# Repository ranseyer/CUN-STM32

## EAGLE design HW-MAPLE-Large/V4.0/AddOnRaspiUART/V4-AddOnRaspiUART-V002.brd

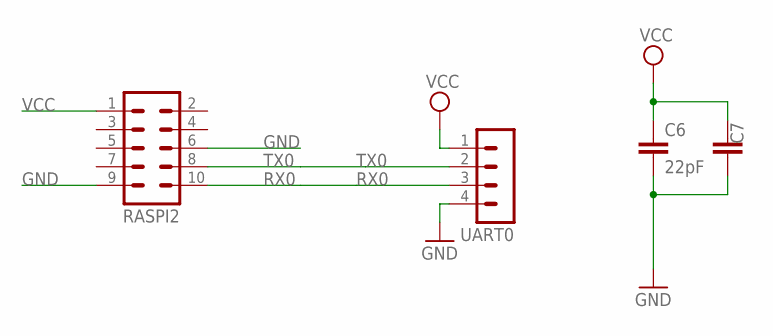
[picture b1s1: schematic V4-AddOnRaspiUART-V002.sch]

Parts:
C6: 22pF; C0805
C7: C-EUC1812; C1812
RASPI2: MA05-2
UART0: MA04-1

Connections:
GND: C6.2, C7.1, RASPI2.6, RASPI2.9, UART0.4
RX0: RASPI2.10, UART0.3
TX0: RASPI2.8, UART0.2
VCC: C6.1, C7.2, RASPI2.1, UART0.1

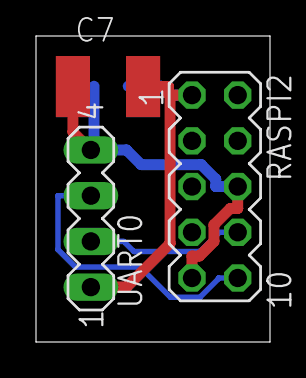
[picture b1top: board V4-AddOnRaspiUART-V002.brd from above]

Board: 2 copper layers, 13.0 x 17.0 mm, 4 parts (1 on the bottom side), 4 nets.

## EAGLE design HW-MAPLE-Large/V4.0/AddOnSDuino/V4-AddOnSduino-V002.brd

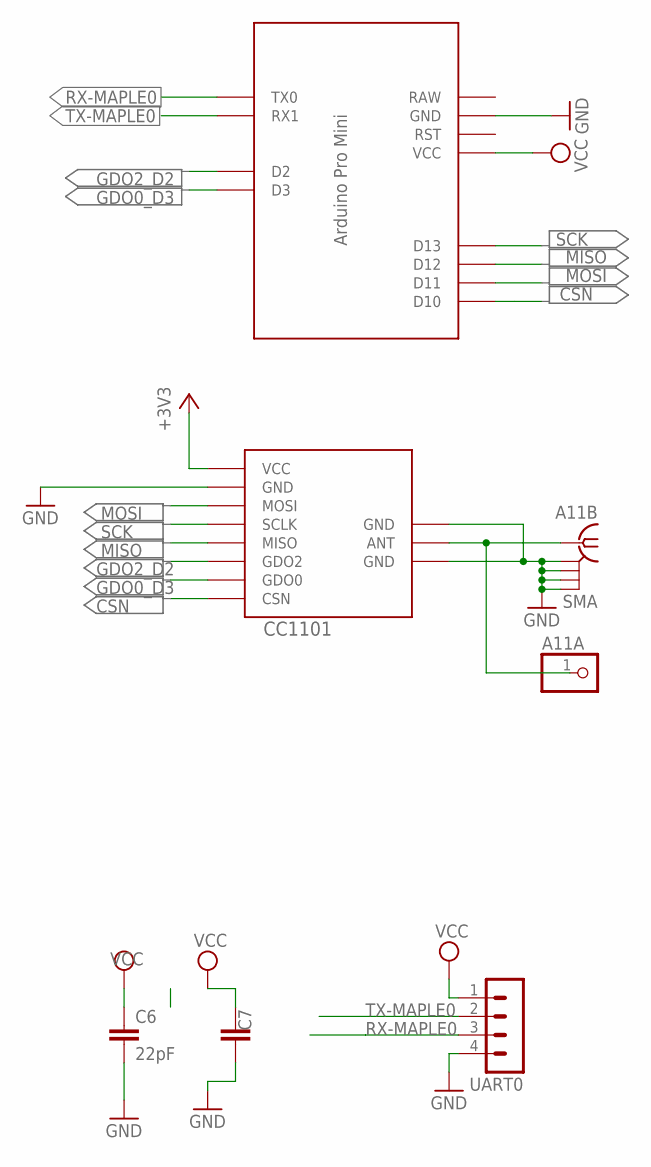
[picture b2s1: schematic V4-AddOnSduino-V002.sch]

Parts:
A11A: PINHD-1X1; 1X01
A11B: SMA
C6: 22pF; C0805
C7: C-EUC1812; C1812
CC1101: CC1101_MODULE1SMD; CC1101_MODULE1_SMD
U$2: MARTIN-PROMINI-CC1101; MARTIN-PRO-CC1101
UART0: MA04-1

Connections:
+3V3: CC1101.VCC
ANT1: A11A.1, A11B.1, CC1101.ANT
CSN: CC1101.CSN, U$2.D10
GDO0_D3: CC1101.GDO0, U$2.D3
GDO2_D2: CC1101.GDO2, U$2.D2
GND: A11B.GND@1 (2), A11B.GND@2 (3), A11B.GND@3 (4), A11B.GND@4 (5), C6.2, C7.1, CC1101.GND@0 (GND), CC1101.GND@1 (GND), CC1101.GND@2 (GND), U$2.GND, UART0.4
MISO: CC1101.MISO, U$2.D12
MOSI: CC1101.MOSI, U$2.D11
RX-MAPLE0: U$2.TX0, UART0.3
SCK: CC1101.SCLK, U$2.D13
TX-MAPLE0: U$2.RX1, UART0.2
VCC: C6.1, C7.2, U$2.VCC, UART0.1

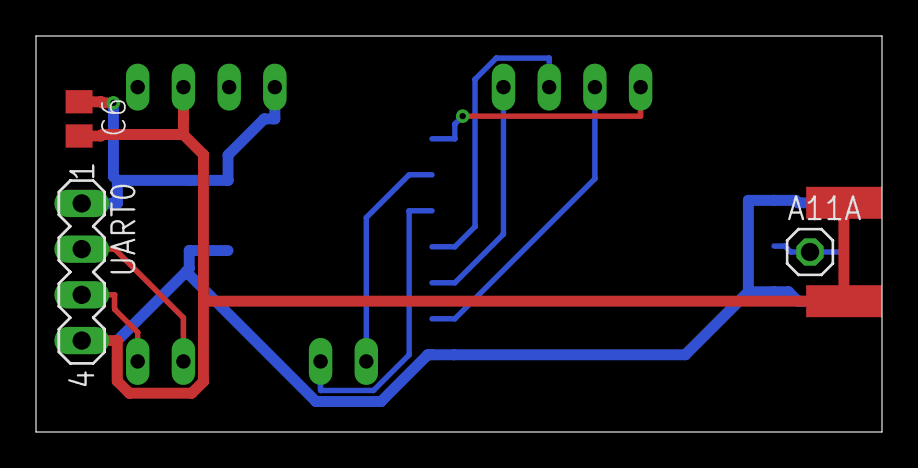
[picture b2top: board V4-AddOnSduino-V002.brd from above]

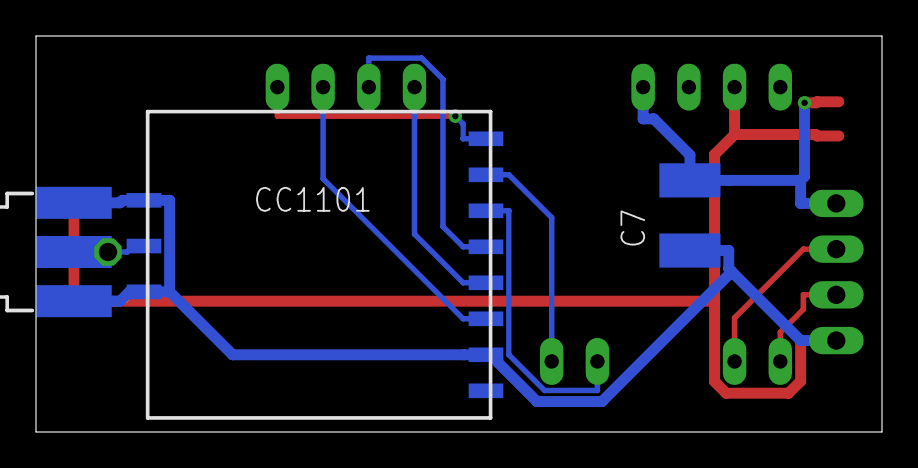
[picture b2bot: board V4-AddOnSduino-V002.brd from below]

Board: 2 copper layers, 47.0 x 22.0 mm, 7 parts (3 on the bottom side), 11 nets.

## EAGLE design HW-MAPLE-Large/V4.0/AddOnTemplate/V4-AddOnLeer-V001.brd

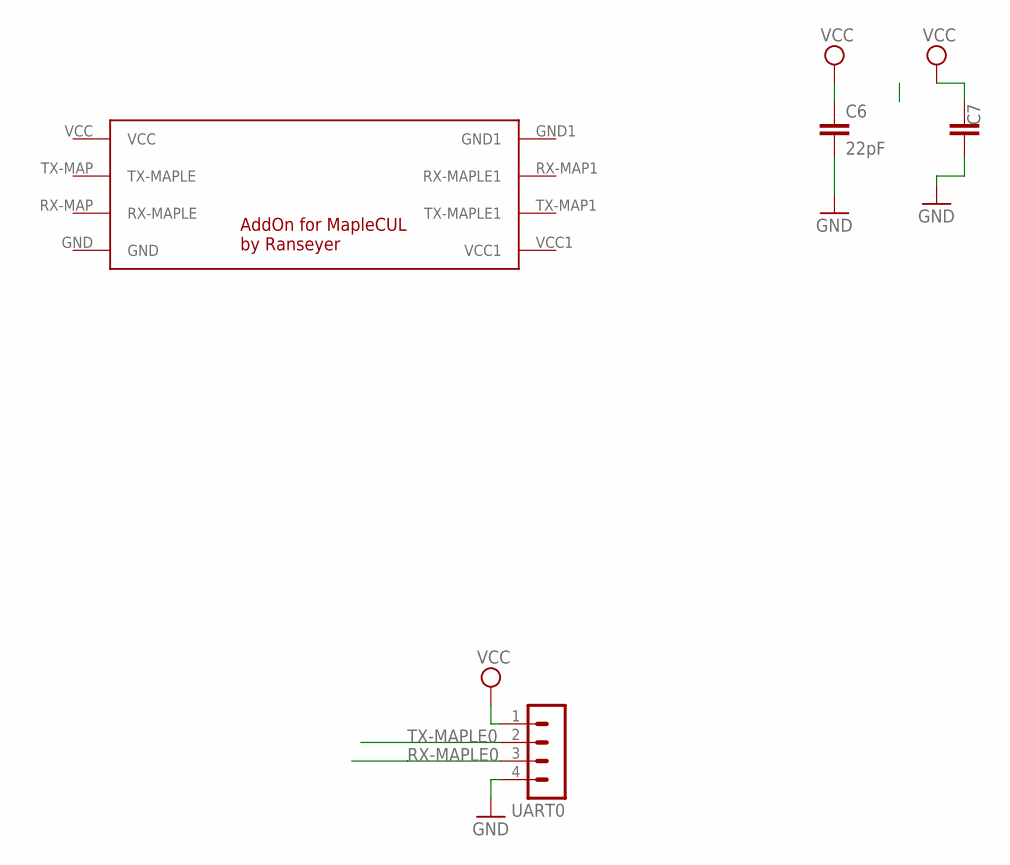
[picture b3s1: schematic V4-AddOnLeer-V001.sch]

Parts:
C6: 22pF; C0805
C7: C-EUC1812; C1812
U$1: MAPLE-CUL-ADDON-V01; MAPLE-CUL-V01
UART0: MA04-1

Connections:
GND: C6.2, C7.1, UART0.4
RX-MAPLE0: UART0.3
TX-MAPLE0: UART0.2
VCC: C6.1, C7.2, UART0.1

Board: 2 copper layers, 4 parts (1 on the bottom side), 2 nets, no tracks yet.

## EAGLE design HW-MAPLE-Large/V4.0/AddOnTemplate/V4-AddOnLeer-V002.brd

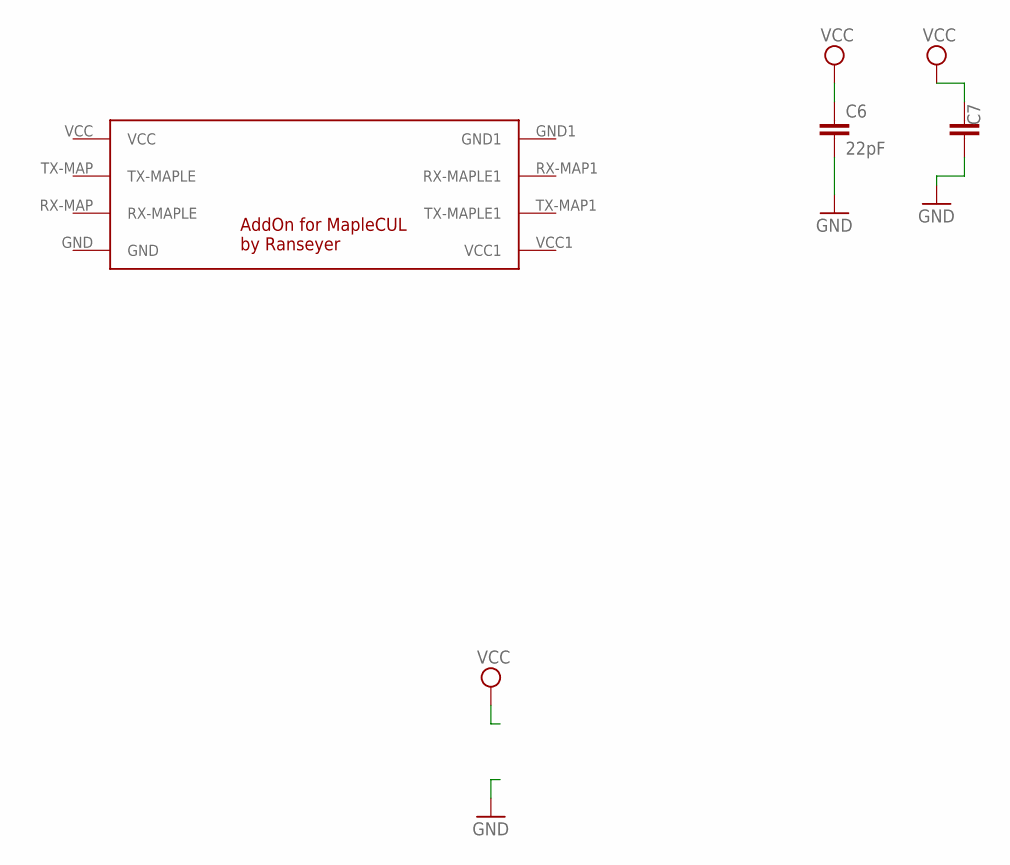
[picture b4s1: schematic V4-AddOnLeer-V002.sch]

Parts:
C6: 22pF; C0805
C7: C-EUC1812; C1812
U$1: MAPLE-CUL-ADDON-V01; MAPLE-CUL-V01

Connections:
GND: C6.2, C7.1
VCC: C6.1, C7.2

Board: 2 copper layers, 3 parts (1 on the bottom side), 2 nets, no tracks yet.

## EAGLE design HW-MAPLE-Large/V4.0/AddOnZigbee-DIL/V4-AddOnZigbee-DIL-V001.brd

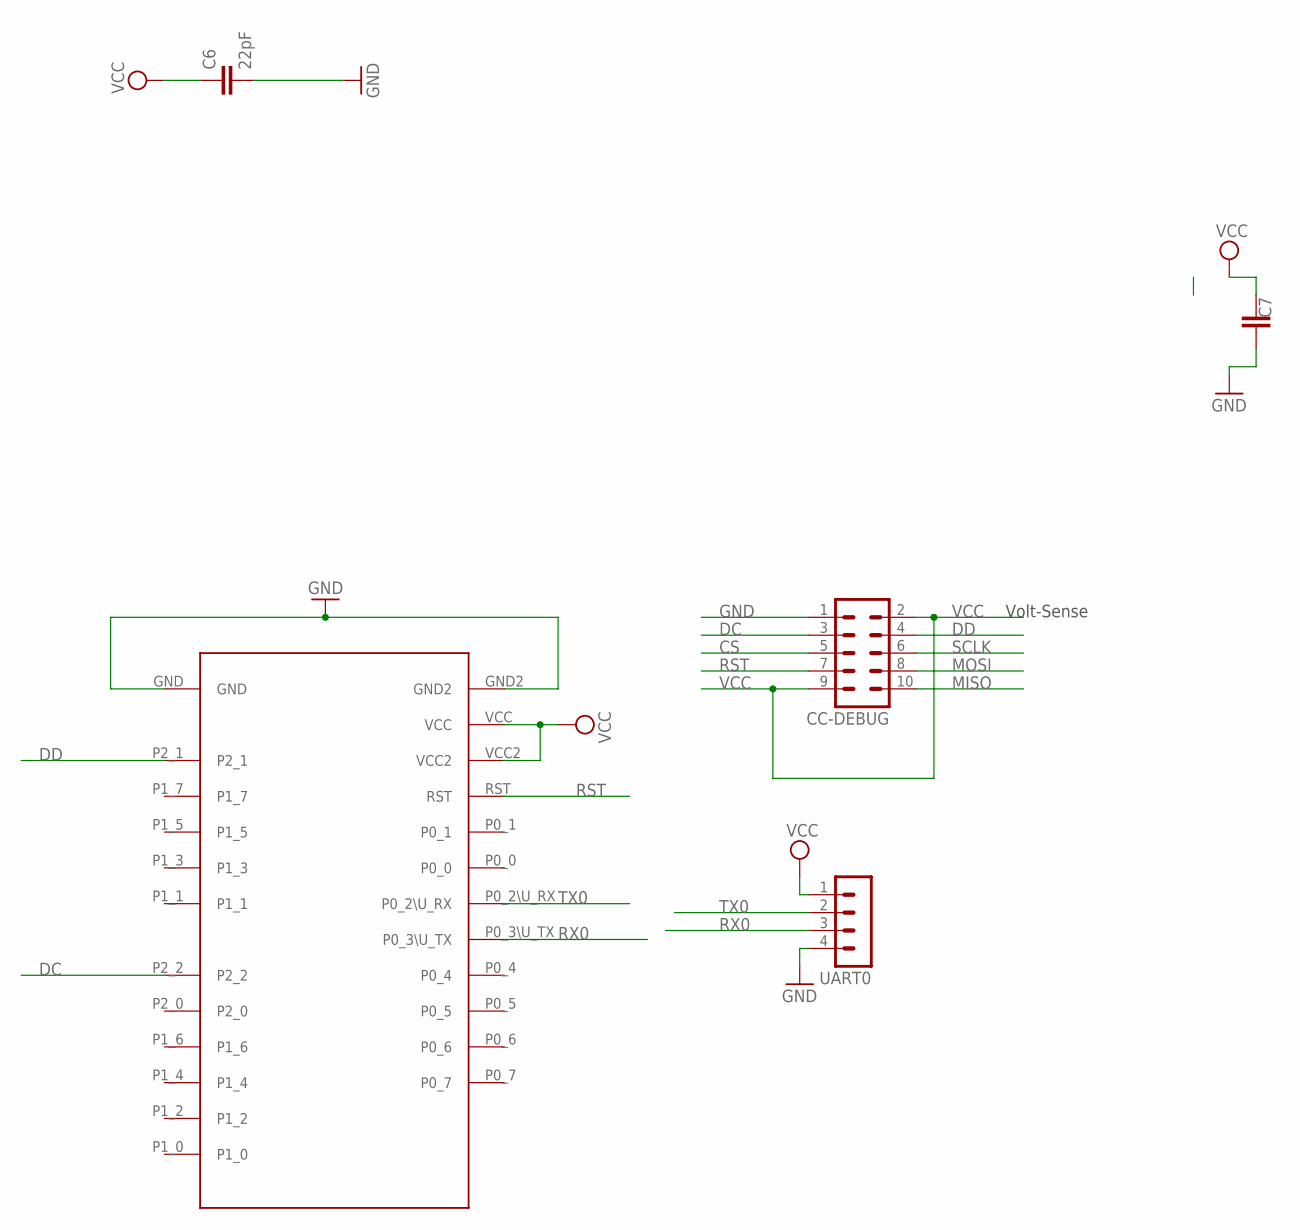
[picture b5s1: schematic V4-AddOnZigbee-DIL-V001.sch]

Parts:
C6: 22pF; C0805
C7: C-EUC1812; C1812
CC-DEBUG: MA05-2
U$3: CC2530_MODULE; CC2530_DIL
UART0: MA04-1

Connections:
CS: CC-DEBUG.5
DC: CC-DEBUG.3, U$3.P2_2
DD: CC-DEBUG.4, U$3.P2_1
GND: C6.2, C7.1, CC-DEBUG.1, U$3.GND, U$3.GND2, UART0.4
MISO: CC-DEBUG.10
MOSI: CC-DEBUG.8
RST: CC-DEBUG.7, U$3.RST
RX0: U$3.P0_3\U_TX, UART0.3
SCLK: CC-DEBUG.6
TX0: U$3.P0_2\U_RX, UART0.2
VCC: C6.1, C7.2, CC-DEBUG.2, CC-DEBUG.9, U$3.VCC, U$3.VCC2, UART0.1

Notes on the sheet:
Volt-Sense

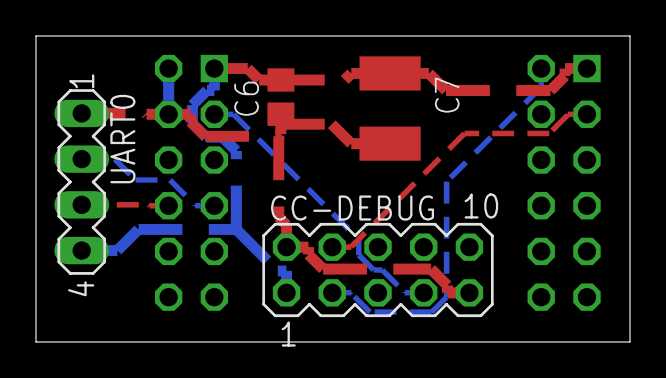
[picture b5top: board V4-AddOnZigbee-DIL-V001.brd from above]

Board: 2 copper layers, 33.0 x 17.0 mm, 5 parts (1 on the bottom side), 7 nets.

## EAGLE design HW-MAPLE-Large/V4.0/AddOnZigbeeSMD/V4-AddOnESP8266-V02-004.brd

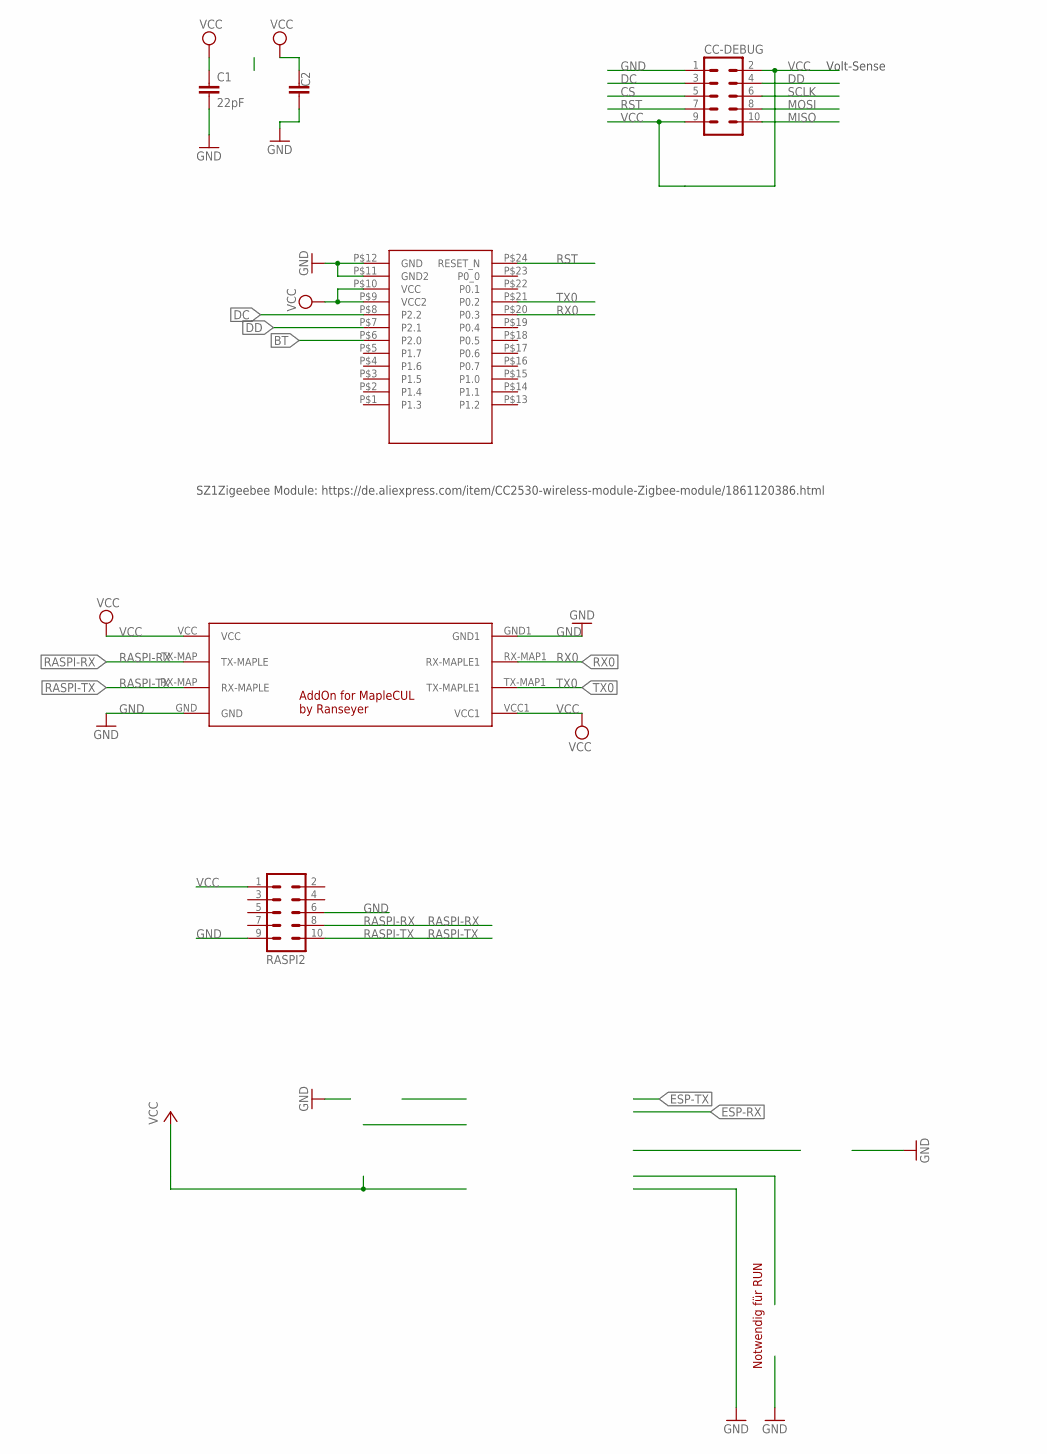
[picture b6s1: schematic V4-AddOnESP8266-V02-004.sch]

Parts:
C1: 22pF; C0805
C2: C-EUC1812; C1812
CC-DEBUG: CONN_05X2SHD_LOCK; 2X5-SHROUDED_LOCK
RASPI2: MA05-2
U$1: MAPLE-CUL-ADDON-V01; MAPLE-CUL-V01
U$2: CC2530; SZ1ZIGBEE-SMD

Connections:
BT: U$2.P$6 (P2.0)
CS: CC-DEBUG.5
DC: CC-DEBUG.3, U$2.P$8 (P2.2)
DD: CC-DEBUG.4, U$2.P$7 (P2.1)
GND: C1.2, C2.1, CC-DEBUG.1, RASPI2.6, RASPI2.9, U$1.GND, U$1.GND1, U$2.P$11 (GND2), U$2.P$12 (GND)
MISO: CC-DEBUG.10
MOSI: CC-DEBUG.8
RASPI-RX: RASPI2.8, U$1.TX-MAP (TX-MAPLE)
RASPI-TX: RASPI2.10, U$1.RX-MAP (RX-MAPLE)
RST: CC-DEBUG.7, U$2.P$24 (RESET_N)
RX0: U$1.RX-MAP1 (RX-MAPLE1), U$2.P$20 (P0.3)
SCLK: CC-DEBUG.6
TX0: U$1.TX-MAP1 (TX-MAPLE1), U$2.P$21 (P0.2)
VCC: C1.1, C2.2, CC-DEBUG.2, CC-DEBUG.9, RASPI2.1, U$1.VCC, U$1.VCC1, U$2.P$9 (VCC2), U$2.P$10 (VCC)

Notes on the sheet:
Volt-Sense
SZ1Zigeebee Module: https://de.aliexpress.com/item/CC2530-wireless-module-Zigbee-module/1861120386.html
Notwendig für RUN

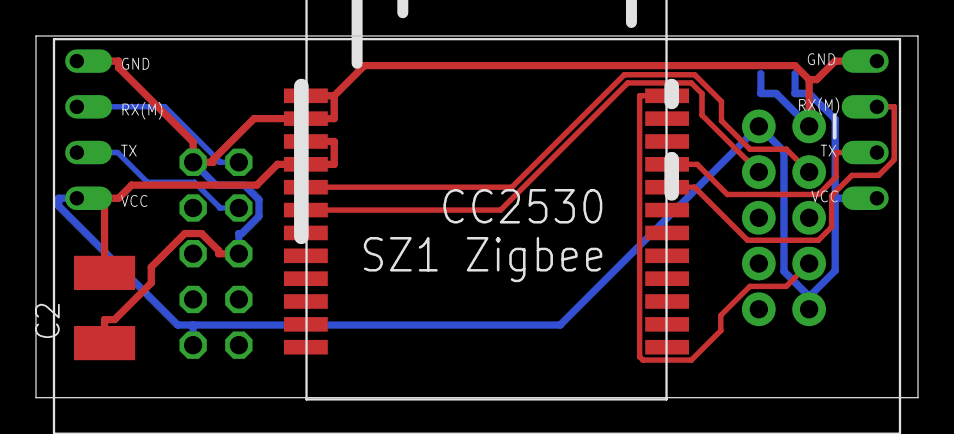
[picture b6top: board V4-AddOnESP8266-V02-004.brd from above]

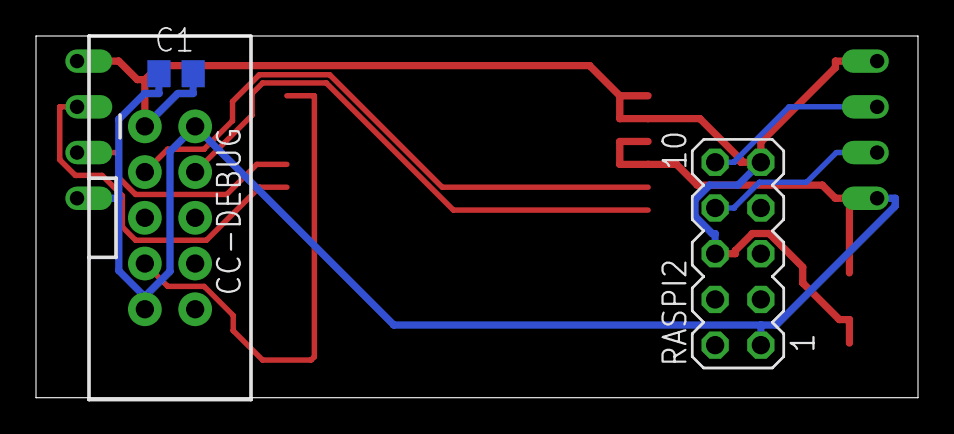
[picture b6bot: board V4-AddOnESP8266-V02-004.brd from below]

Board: 2 copper layers, 49.0 x 20.1 mm, 6 parts (3 on the bottom side), 9 nets.

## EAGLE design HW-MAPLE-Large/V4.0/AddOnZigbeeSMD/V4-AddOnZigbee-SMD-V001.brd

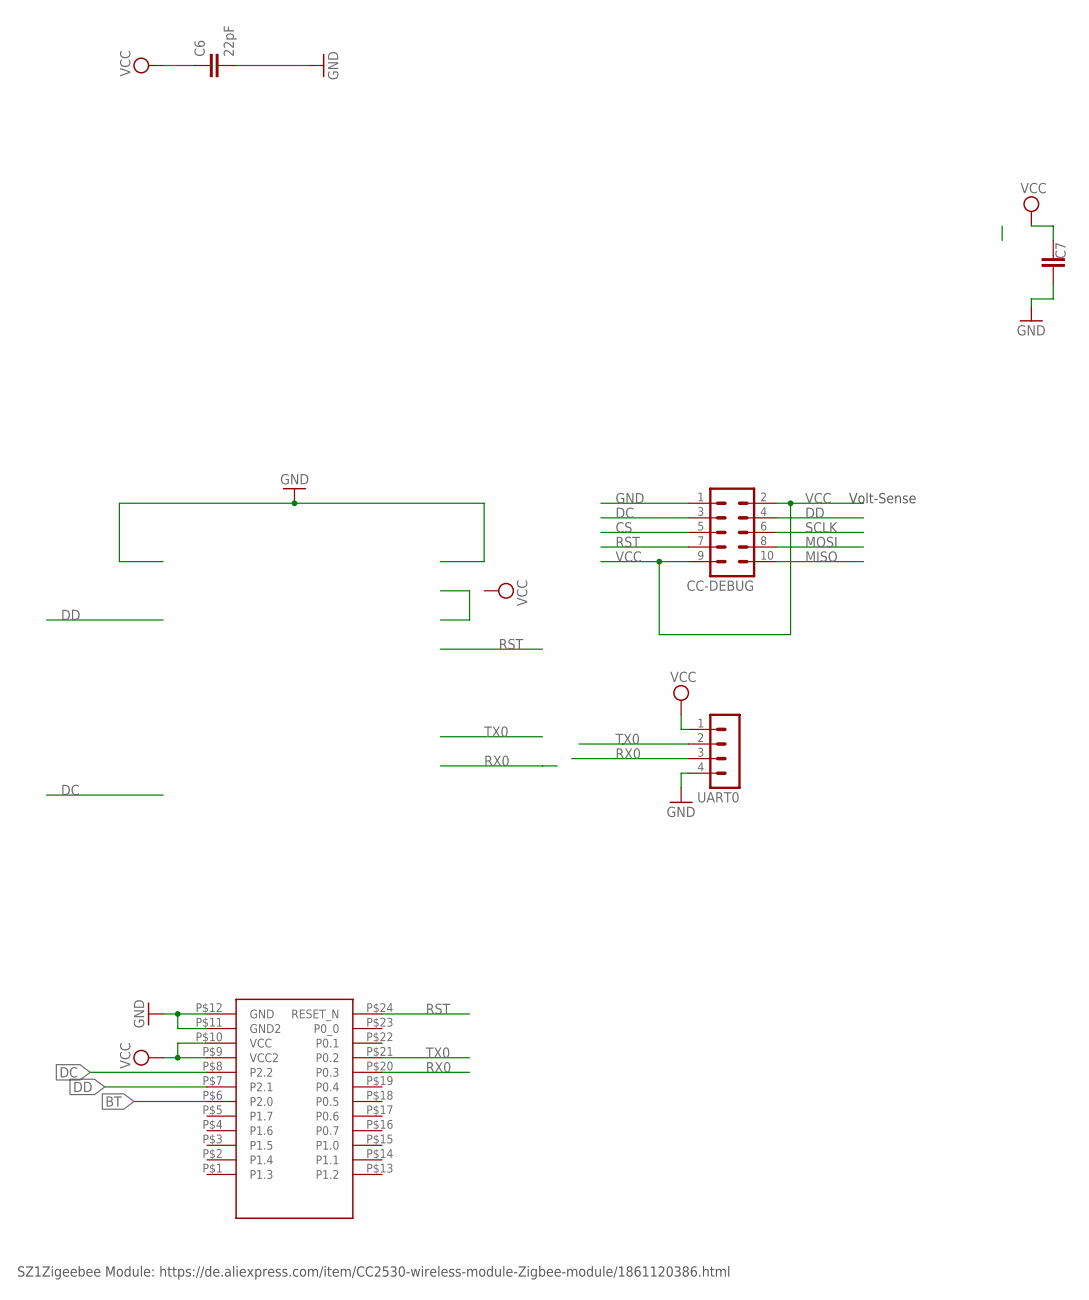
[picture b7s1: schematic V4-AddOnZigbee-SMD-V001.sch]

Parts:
C6: 22pF; C0805
C7: C-EUC1812; C1812
CC-DEBUG: MA05-2
U$1: CC2530CC2530PA; CC2530PA
UART0: MA04-1

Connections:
BT: U$1.P$6 (P2.0)
CS: CC-DEBUG.5
DC: CC-DEBUG.3, U$1.P$8 (P2.2)
DD: CC-DEBUG.4, U$1.P$7 (P2.1)
GND: C6.2, C7.1, CC-DEBUG.1, U$1.P$11 (GND2), U$1.P$12 (GND), UART0.4
MISO: CC-DEBUG.10
MOSI: CC-DEBUG.8
RST: CC-DEBUG.7, U$1.P$24 (RESET_N)
RX0: U$1.P$20 (P0.3), UART0.3
SCLK: CC-DEBUG.6
TX0: U$1.P$21 (P0.2), UART0.2
VCC: C6.1, C7.2, CC-DEBUG.2, CC-DEBUG.9, U$1.P$9 (VCC2), U$1.P$10 (VCC), UART0.1

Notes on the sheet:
Volt-Sense
SZ1Zigeebee Module: https://de.aliexpress.com/item/CC2530-wireless-module-Zigbee-module/1861120386.html

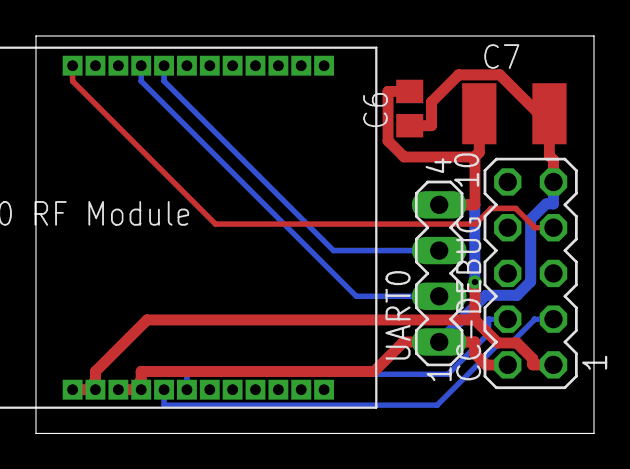
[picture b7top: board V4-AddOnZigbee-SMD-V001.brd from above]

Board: 2 copper layers, 31.0 x 22.1 mm, 5 parts (0 on the bottom side), 7 nets.

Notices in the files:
parts and their libraries:
SparkFun-Connectors: Licensing: Creative Commons ShareAlike 4.0 International - https://creativecommons.org/licenses/by-sa/4.0
